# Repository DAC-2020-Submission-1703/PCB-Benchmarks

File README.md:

# PCB-Benchmarks

These are PCB benchmarks for automated layout as described in DAC 2020 submission 1703.
We have made efforts to anonymize this repo to facilitate the blind academic review process or DAC. The full repo will be updated with author information and so on after the review period.

## Metrics
The primary metrics for PCB layout are through-hole via count, required routing layers, required laser via layers, and area of the smallest rectangular bounding box. These metrics affect manufacturing cost.

A secondary metric is routed track length. It does not affect cost or correctness for these low-speed designs, but may be useful for evaluating the quality of a placement.

## Technical details
Each benchmark is manually placed and routed. 
To use as a layout benchmark, remove the manual routing and ignore the manual placement.

Each design is based on a real design that has been manufactured and tested. The designs in this repo have been modified from the originals to facillitate their use as layout benchmarks.

Each has a board outline in the Edge.Cuts layer. Each component has one or more courtyard polygons in the F.CrtYd and B.CrtYd layers if applicable.

Copper pours ("zones") have been removed from the designs. Nets that used zones for connectivity have been manually rerouted.

The manual routing jobs do not require laser vias; only through-hole vias are used.

Some components are "locked" as indicated by the locked keyword in their definition. These components must not be moved during automated placement.

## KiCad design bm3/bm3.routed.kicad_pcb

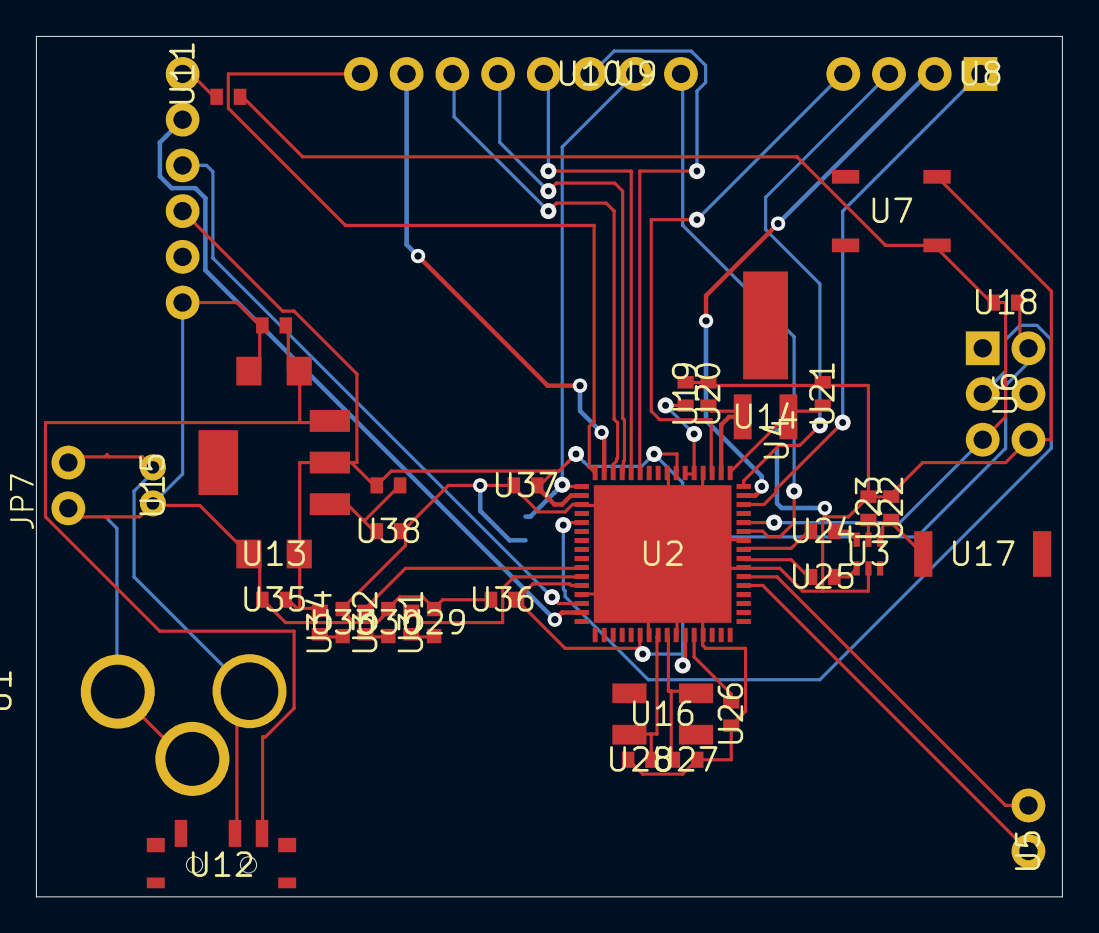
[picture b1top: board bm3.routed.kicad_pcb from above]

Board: 2 copper layers, 57.0 x 47.8 mm, 40 parts (0 on the bottom side), 38 nets.

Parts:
JP7: 1X02_NO_SILK
SJ1: SJ_2S-TRACE
U1: POWER_JACK_PTH_LOCK
U2: QFN-64
U3: BALUN
U4: SJ_2S-TRACE
U5, U9: 1X02_NO_SILK
U6: 2X3-NS
U7: TACTILE_SWITCH_SMD
U8: 1X04_NO_SILK
U10: 1X06_NS
U11: FTDI_BASIC
U12: SWITCH-SPST-SMD-A
U13: EIA3216
U14: CRYSTAL-32KHZ-SMD
U15: JST-2-PTH
U16: CRYSTAL-SMD-5X3
U17: ANTENNA-CHIP5
U18, U31, U32, U34, U38: 0402-RES
U19, U20, U21, U22, U23, U24, U25, U26, U27, U28, U35, U36, U37: 0402-CAP
U29, U30, U33: LED-0603

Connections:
3.3V: U2.23, U2.34, U2.44, U2.54, U2.59, U6.2, U11.VCC, U13.A, U18.2, U34.2, U35.1, U36.1, U37.1
A6: U2.5, U5.1
A7: U2.6, U5.2
AVDD: U2.60, U26.1
CLKI: SJ1.2, U2.33, U9.1
DVDD: U2.21, U2.22, U19.1
GND: JP7.1, SJ1.1, U1.GND, U1.GNDBREAK, U2.7, U2.10, U2.20, U2.24, U2.35, U2.45, U2.55, U2.58, U2.61, U2.65, U3.5, U4.1, U6.6, U7.3, U11.GND, U13.C, U15.1, U19.2, U20.2, U21.2, U22.1, U23.2, U26.2, U27.2, U28.2, U29.C, U30.C, U33.C, U35.2, U36.2, U37.2, U38.1
unnamed: U33.A, U34.1
unnamed: U2.57, U16.3, U27.1
unnamed: U2.56, U16.1, U28.1
unnamed: U2.18, U14.X1, U20.1
unnamed: U2.17, U14.X2, U21.1
unnamed: U3.2, U23.1
unnamed: U30.A, U32.1
unnamed: JP7.2, U1.PWR, U12.2, U15.2
unnamed: U3.4, U25.2
unnamed: U3.3, U24.1
unnamed: U29.A, U31.1
PB6: U2.42, U32.2
PB7: U2.43, U31.2
PD4: U2.29, U10.3
PD5: U2.30, U10.4
PD6: U2.31, U10.5
PD7: U2.32, U10.6
PG0: U2.14, U8.1
PG1: U2.15, U8.2
PG2: U2.16, U8.3
PG5: U2.19, U8.4
RESET: U2.12, U6.5, U7.1, U18.1
RFANT: U3.1, U17.FEED, U22.2
RFN: U2.9, U24.2
RFP: U2.8, U25.1
RX0: U2.46, U11.TXO
RX1: U2.27, U10.1
SCK: U2.37, U6.3
TST: U2.11, U4.2, U9.2
TX0: U2.47, U11.RXI
TX1: U2.28, U10.2

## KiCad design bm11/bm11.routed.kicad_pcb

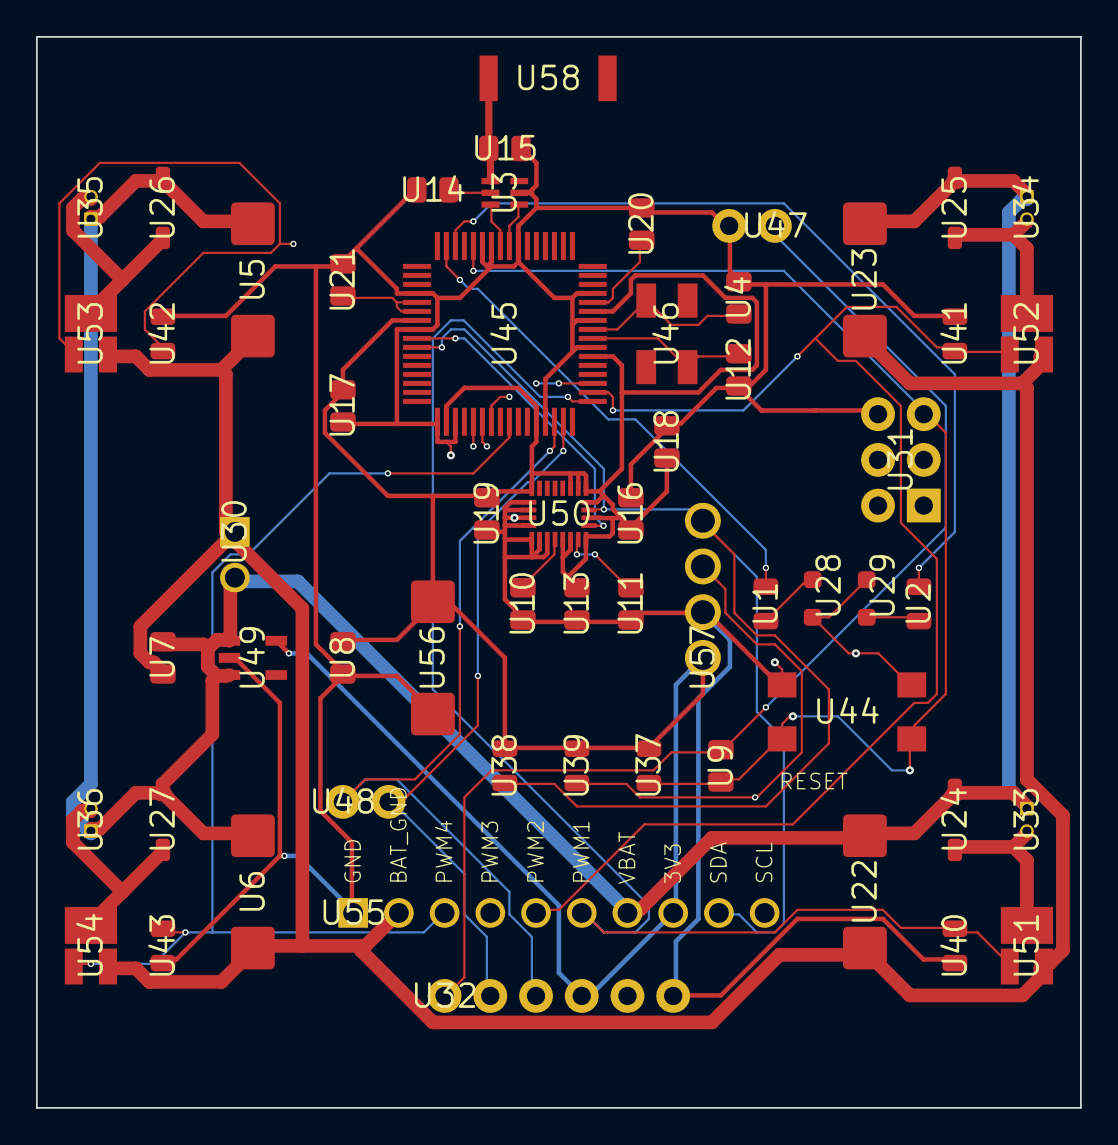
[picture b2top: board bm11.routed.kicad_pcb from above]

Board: 4 copper layers, 58.0 x 59.5 mm, 58 parts (0 on the bottom side), 35 nets.

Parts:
U1, U2, U37, U38, U39, U40, U41, U42, U43: RESC2012X60_HS
U3: BALUN
U4, U7, U8, U9, U10, U11, U12, U13, U14, U15, U16, U17, U18, U19, U20, U21: CAPC2012X140_HS
U5, U6, U22, U23, U56: CAPMP7343X310_HS
U24, U25, U26, U27: SOD3716X135_HS
U28, U29: LEDSC125X200X120-2_HS
U30: MALE_HEADER_2X1_0.1IN
U31: 2X3-NS
U32: FTDI_BASIC
U33, U34, U35, U36: MOLEX-0530470210
U44: 4.5MM_TACTILE_SWITCH_TL3305AF160QG
U45: QFN-64
U46: CRYSTAL-SMD-5X3
U47: FTDI_BASIC_2PIN_2
U48: FTDI_BASIC_2PIN_1
U49: SOT23-DBV
U50: NEW_IMU_MEDIUM
U51, U52, U53, U54: N_FET_SI2302CDS-T1-E3CT-ND
U55: HDRV10W63P254_10X1_2540X254H838_HS
U57: HDRVR4W80P254_1X4_1066X254X850B
U58: ANT-2.4GHZ-6.5X2.2MM

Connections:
3V3: U8.1, U13.1, U16.1, U17.1, U18.1, U19.1, U32.VCC, U37.2, U38.2, U39.2, U45.23, U45.34, U45.44, U45.54, U45.59, U49.5, U50.CS_A/G, U50.CS_M, U50.DEN_A/G, U50.SDO_A/G, U50.SDO_M, U50.VDD1, U50.VDD2, U50.VDDIO, U50.VDDIO2, U55.8, U56.1, U57.1
/DTR: U9.1, U32.DTR, U47.DTR
/LED1: U2.2, U45.14
/LED2: U1.2, U45.15
/MISO: U31.1, U45.39
/MOSI: U31.4, U45.38
/PWM1: U40.1, U45.49, U51.G, U55.6
/PWM2: U41.1, U45.50, U52.G, U55.5
/PWM3: U42.1, U45.51, U53.G, U55.4
/PWM4: U43.1, U45.41, U54.G, U55.3
/RESET: U9.2, U31.5, U37.1, U44.3, U44.4, U45.12
/RX0: U32.TXO, U45.46, U48.TXO
/SCK: U31.3, U45.37
/SCL: U39.1, U45.25, U50.SCL/SPC, U55.10, U57.3
/SDA: U38.1, U45.26, U50.SDA/SDI/SDO, U55.9, U57.4
/TX0: U32.RXI, U45.47, U48.RXI
BAT_GND: U5.2, U6.2, U7.2, U22.2, U23.2, U30.1, U51.S, U52.S, U53.S, U54.S, U55.2
GND: U3.5, U4.2, U8.2, U10.2, U11.2, U12.2, U13.2, U14.2, U15.2, U16.2, U17.2, U18.2, U19.2, U20.2, U21.2, U28.2, U29.1, U31.6, U32.GND, U40.2, U41.2, U42.2, U43.2, U44.1, U44.2, U45.7, U45.10, U45.11, U45.20, U45.24, U45.33, U45.35, U45.45, U45.55, U45.58, U45.61, U47.CTS, U49.2, U50.GND1, U50.GND2, U50.RES1, U50.RES2, U50.RES3, U50.RES4, U50.RES5, U55.1, U56.2, U57.2
unnamed: U3.1, U15.1, U58.FEED
unnamed: U3.2, U14.1
unnamed: U3.3, U45.9
unnamed: U3.4, U45.8
unnamed: U4.1, U45.57, U46.1
unnamed: U12.1, U45.56, U46.3
unnamed: U20.1, U45.60
unnamed: U21.1, U45.21, U45.22
unnamed: U10.1, U50.CAP
unnamed: U11.1, U50.C1
unnamed: U24.A, U33.2, U51.D
unnamed: U25.A, U34.2, U52.D
unnamed: U26.A, U35.2, U53.D
unnamed: U27.A, U36.2, U54.D
unnamed: U1.1, U28.1
unnamed: U2.1, U29.2
VBAT: U5.1, U6.1, U7.1, U22.1, U23.1, U24.C, U25.C, U26.C, U27.C, U30.2, U33.1, U34.1, U35.1, U36.1, U49.1, U49.3, U55.7

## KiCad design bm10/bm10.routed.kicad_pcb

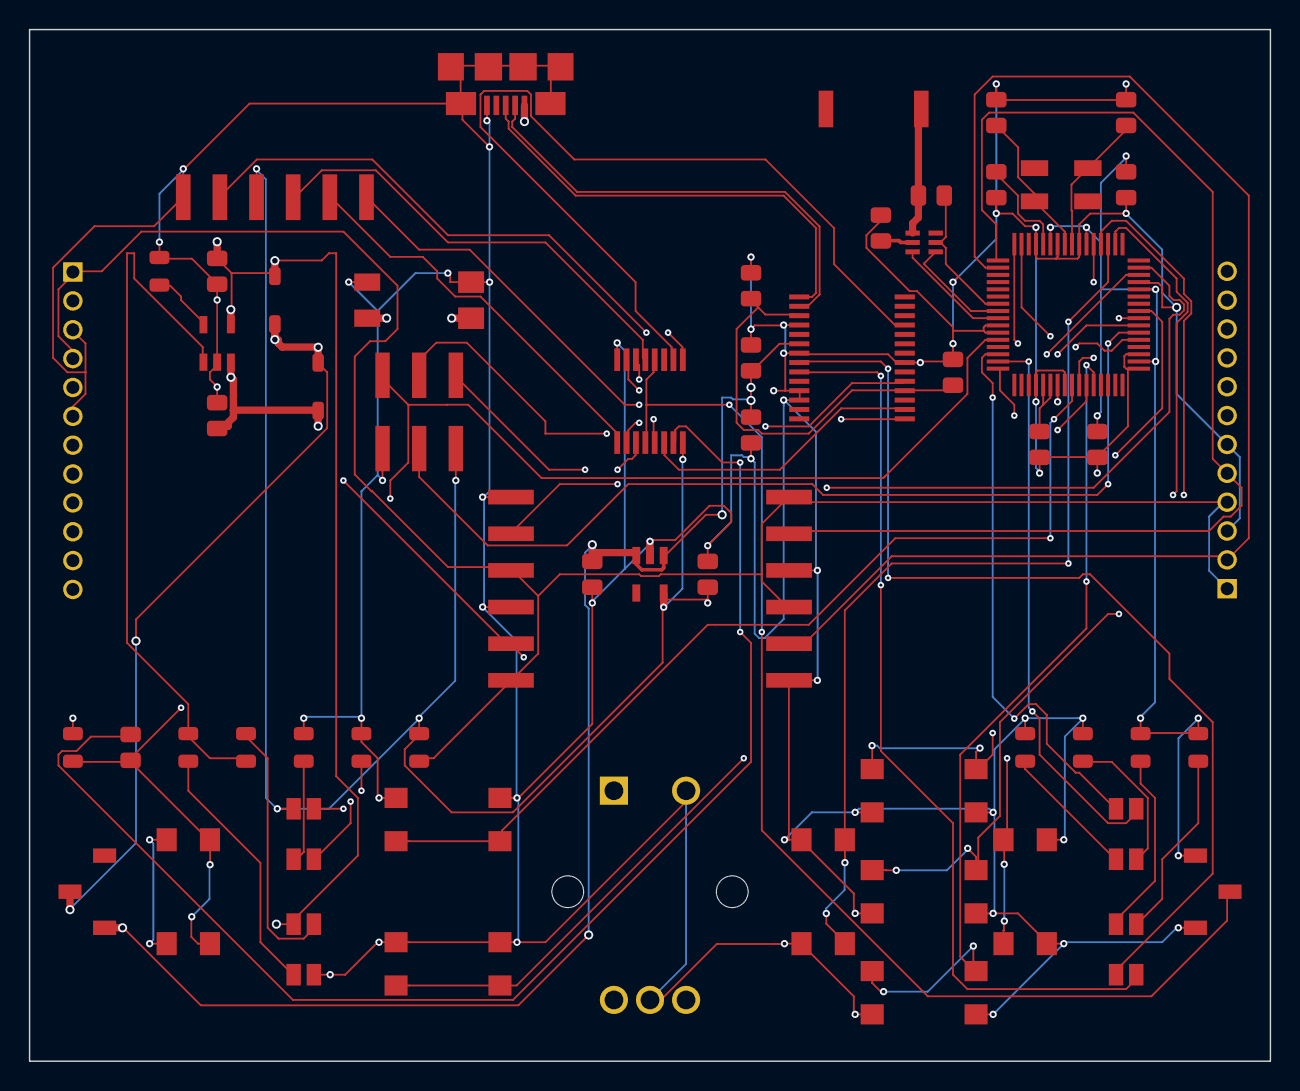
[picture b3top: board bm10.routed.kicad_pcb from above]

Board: 4 copper layers, 86.0 x 71.5 mm, 61 parts (0 on the bottom side), 63 nets.

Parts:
A1: ANTENNA-CHIP; ANT-2.4GHZ-6.5X2.2MM
B1, B4, B5, B6, B7, B8, B9, B10: PUSHBUTTON_-4.5X4.5; 4.5MM_TACTILE_SWITCH_TL3305AF160QG
B2: BALUN0805; BALUN
B3: BATTERY-SPRING-SMD; WIRE-TERMINAL-1X2-2.5MM-SMD-AVX-009276002021106
C1, C8, C9: 0.1uF; CAPC2012X140_HS
C2: 0.75pF; CAPC2012X140_HS
C3: 22pF; CAPC2012X140_HS
C4, C10, C11, C12, C13, C16, C17: 1uF; CAPC2012X140_HS
C5, C6, C7: 10uF; CAPC2012X140_HS
C14, C15: 12pF; CAPC2012X140_HS
D1, D4, D5, D6: LED-2X-GREEN_RED; LED-2X-LTST-C155
D2, D3: 360mV; SOD3716X135_HS
E1: ROTARY-ENCODER-W_BUTTON-BOURNS-PEC12R-4217F; BOURNS-PEC12R
J1: USB-MICROA-AMPHENOL-10118192-0001LF; USB-MICROA-10118192-0001LF
J2, J3: 2.4K; JST-13-PTH
J4: AVR_SPI_PRG_6-SMD; 2X3-SMD
J7, J8: FRSKY-GIMBAL-2X-SERVO-SMD; 2X-SERVO-SMD
JP1: FTDI_BASIC-SMD; FTDI-BASIC-SMD
R1, R3, R13, R14, R15, R16, R17, R18: 510; RESC2012X60_HS
R2: 10K; RESC2012X60_HS
R7: 2.2K; RESC2012X60_HS
R8: 1.2K; RESC2012X60_HS
S1, S2: POWER-SWITCH-MFS201N-9-Z-SMD-VERTICAL; JS102011JCQN
U1: 3.3V; SOT23-DBV
U2: MCP73831T-2ACI/OT; SOT23-5
U3: FT232RLSSOP; SSOP28DB
U4: ATMEGA128RFA1; QFN-64
U5: DPDT-X2; SOP65P640X110-16
Y1: CRYSTAL5X3; CRYSTAL-SMD-5X3

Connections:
3V3: C12.1, C16.1, C17.1, D4.A2, J4.2, JP1.VCC, R2.2, R8.2, R13.2, R14.2, S2.1, U1.5, U4.23, U4.34, U4.44, U4.54, U4.59, U5.16
/BTN1/SCL: B4.3, B4.4, U4.25
/BTN2/SDA: B5.3, B5.4, U4.26
/BTN_CENTER: B9.1, B9.2, U4.53
/BTN_DOWN: B10.1, B10.2, U4.28
/BTN_LEFT: B7.1, B7.2, U4.51
/BTN_RIGHT: B8.1, B8.2, U4.52
/BTN_UP: B6.1, B6.2, U4.50
/CTS: U3.11, U5.2
/CTS-1: JP1.CTS, U5.1
/DTR: U3.2, U5.14
/DTR-0: C1.2, U5.15
/DTR-1: JP1.DTR, U5.13
/E1-A: E1.A, U4.40
/E1-B: E1.B, U4.41
/E1-BUT: E1.BUTA, U4.27
/FTDI_OUT: C4.2, C9.1, U3.4, U3.17
/GREF: J2.1, J2.4, J3.1, J3.4, J7.1, J7.4, J8.1, J8.4, R8.1
/MISO: J4.1, U4.39
/MOSI: J4.4, U4.38
/PITCH: J3.V, J8.V, U4.2
/RESET: B1.1, B1.2, C1.1, J4.5, R2.1, U4.12
/RF: D4.A1, U4.16
/ROLL: J3.H, J8.H, U4.1
/RXI: U3.5, U5.10
/RXI-0: U4.47, U5.11
/RXI-1: JP1.RXI, U5.9
/RXLED: D5.C2, U3.22
/SCK: J4.3, U4.37
/THROTTLE: J2.V, J7.V, U4.64
/TXLED: D5.C1, U3.23
/TXO: U3.1, U5.6
/TXO-0: U4.46, U5.7
/TXO-1: JP1.TXO, U5.5
/USB_D_N: J1.2, U3.16
/USB_D_P: J1.3, U3.15
/VBUS: C5.1, D1.A2, D2.A, J1.1, U2.4
/VREG_IN: C7.1, C8.1, C10.1, S1.1, U1.1, U1.3, U3.20
/YAW: J2.H, J7.H, U4.63
GND: B1.3, B1.4, B2.5, B3.2A, B3.2B, B4.1, B4.2, B5.1, B5.2, B6.3, B6.4, B7.3, B7.4, B8.3, B8.4, B9.3, B9.4, B10.3, B10.4, C2.2, C3.1, C4.1, C5.2, C6.2, C7.2, C8.2, C9.2, C10.2, C11.2, C12.2, C13.2, C14.2, C15.2, C16.2, C17.2, D1.C1, E1.BUTB, E1.C, J1.5, J1.6, J1.7, J1.8, J1.9, J1.10, J1.11, J2.3, J2.6, J3.3, J3.6, J4.6, J7.3, J7.6, J8.3, J8.6, JP1.GND, R7.2, R15.1, R16.1, R17.1, R18.1, S2.3, U1.2, U2.2, U3.7, U3.18, U3.21, U3.25, U3.26, U4.7, U4.10, U4.11, U4.20, U4.24, U4.33, U4.35, U4.45, U4.55, U4.58, U4.61, U5.8
unnamed: A1.FEED, B2.1, C2.1
unnamed: B2.2, C3.2
unnamed: B2.3, U4.9
unnamed: B2.4, U4.8
unnamed: B3.1A, B3.1B, C6.1, D3.A, U2.3
unnamed: C11.1, U4.21, U4.22
unnamed: C13.1, U4.60
unnamed: C14.1, U4.57, Y1.3
unnamed: C15.1, U4.56, Y1.1
unnamed: D1.A1, R3.1
unnamed: D1.C2, R1.1
unnamed: D4.C1, R15.2
unnamed: D4.C2, R16.2
unnamed: D5.A1, R14.1
unnamed: D5.A2, R13.1
unnamed: D6.A1, U4.15
unnamed: D6.A2, U4.14
unnamed: D6.C1, R18.2
unnamed: D6.C2, R17.2
unnamed: R1.2, R3.2, U2.1
unnamed: R7.1, U2.5
unnamed: S2.2, U5.4, U5.12
VBAT: D2.C, D3.C, S1.2

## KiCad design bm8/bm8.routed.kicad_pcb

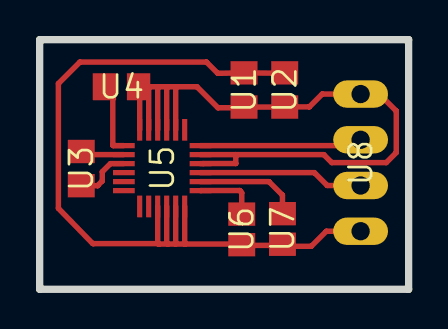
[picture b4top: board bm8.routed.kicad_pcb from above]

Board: 2 copper layers, 20.5 x 13.9 mm, 8 parts (0 on the bottom side), 9 nets.

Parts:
U1, U2, U3, U4: C0805
U5: LGA-24
U6, U7: R0805
U8: MA04-1

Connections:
/SCL: U5.21, U8.2
/SDA: U5.24, U8.3
GND: U1.2, U2.2, U4.1, U5.2, U5.3, U5.4, U5.5, U5.6, U5.22, U5.23, U8.4
unnamed: U3.1, U5.9
unnamed: U3.2, U5.8
unnamed: U4.2, U5.7
unnamed: U5.19, U6.1
unnamed: U5.20, U7.1
VDD: U1.1, U2.1, U5.15, U5.16, U5.17, U5.18, U6.2, U7.2, U8.1

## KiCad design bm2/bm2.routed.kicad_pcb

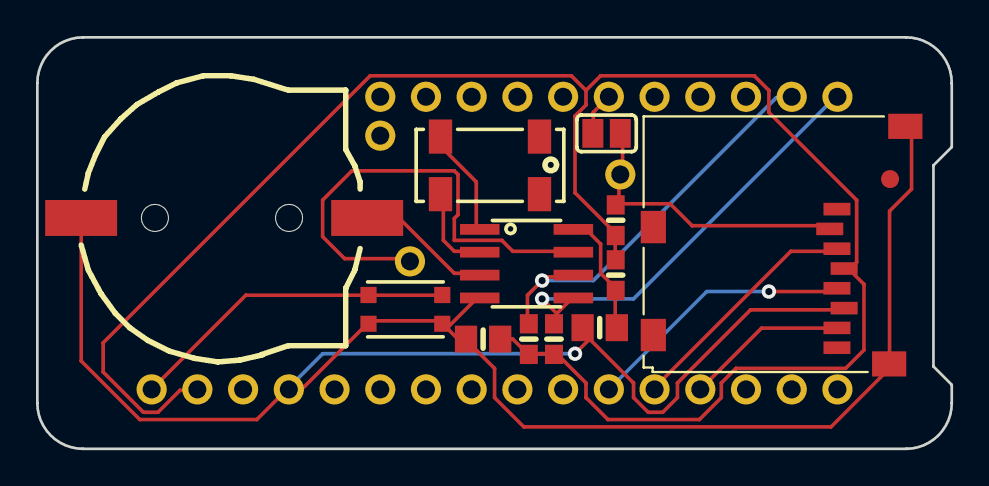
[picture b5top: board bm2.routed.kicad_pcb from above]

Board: 2 copper layers, 50.8 x 22.9 mm, 18 parts (0 on the bottom side), 15 nets.

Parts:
B1: cr1220; CR1220-2
C1, C2: 10uF; 0805-NO
FID1: FIDUCIAL_1MM
IC1: PCF8523T; SOIC8_150MIL
INT1: 1X01_ROUND
JP1: 1X11_ROUND
JP2: 1X16_ROUND
JP3: 1X01_ROUND
R1, R2: 10K; 0603-NO
R3: 100K; 0603-NO
R4: 1K; 0603-NO
SDCS: 1X01_ROUND
SJ1: SOLDERJUMPER_CLOSEDWIRE
SW1: KMR2; BTN_KMR2_4.6X2.8
X4: microsd; MICROSD
Y1: 32khz; CRYSTAL_8X3.8

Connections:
+3V3: C2.1, JP2.15, R1.2, R2.2, R3.2, R4.1, X4.4
CR1220: B1.+, IC1.3
CS: JP1.6, SJ1.1
GND: B1.-, C1.2, C2.2, IC1.4, JP2.13, SW1.A, SW1.A', X4.6, X4.MT1, X4.MT2
INT1: IC1.7, INT1.1
MISO: JP2.4, X4.7
MOSI: JP2.5, X4.3
unnamed: C1.1, IC1.8, R4.2
unnamed: IC1.1, Y1.P$4
unnamed: IC1.2, Y1.P$1
RESET: JP2.16, SW1.B, SW1.B'
SCK: JP2.6, X4.5
SCL: IC1.6, JP1.10, R2.1
SDA: IC1.5, JP1.11, R1.1
SD_CS: R3.1, SDCS.1, SJ1.2, X4.2

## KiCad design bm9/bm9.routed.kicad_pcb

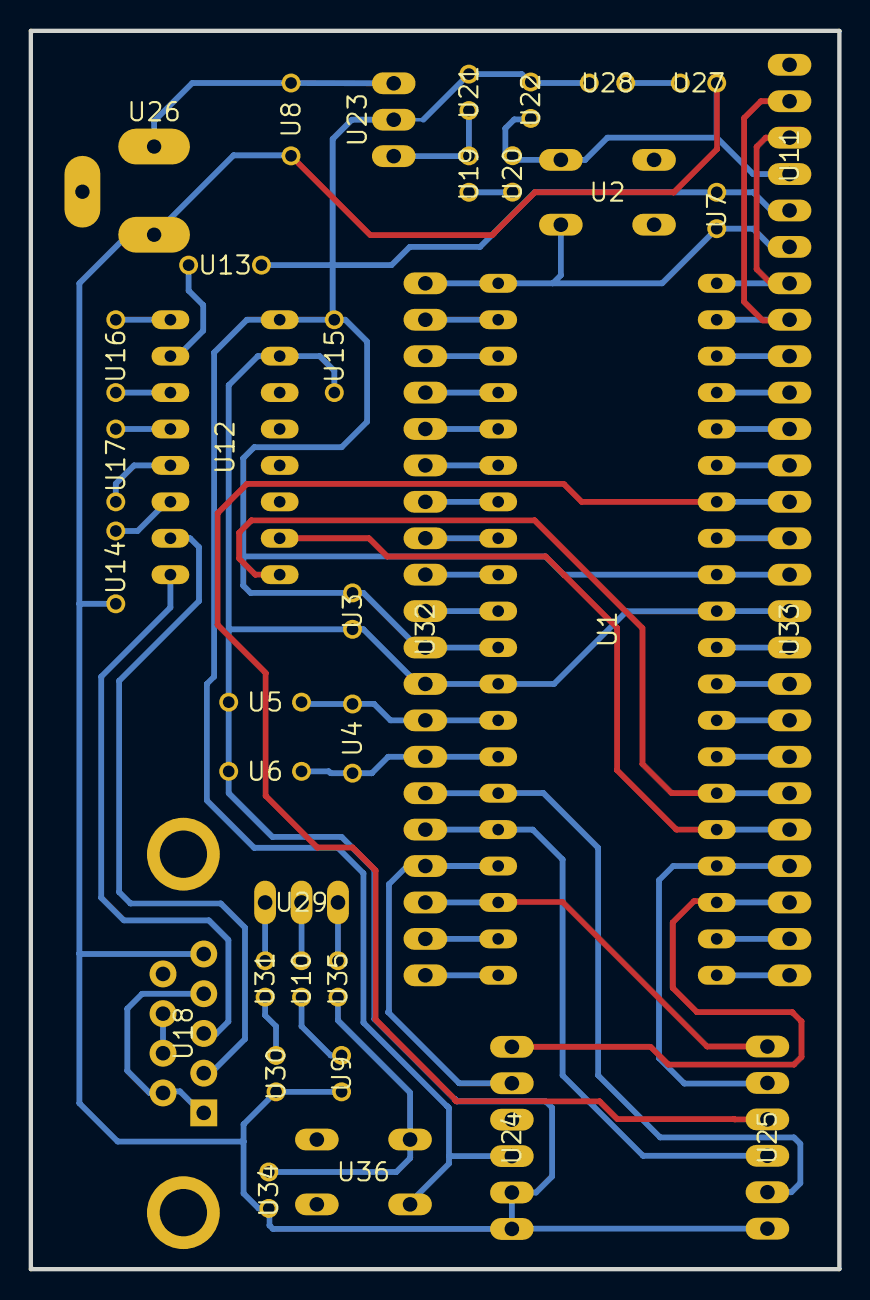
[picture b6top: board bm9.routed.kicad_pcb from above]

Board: 16 copper layers, 56.4 x 86.4 mm, 36 parts (0 on the bottom side), 58 nets.

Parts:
U1: DIL40
U2, U36: B3F-10XX
U3, U22: C025-024X044
U4: HC49_S
U5, U6, U13, U14, U15, U16, U17: C050-024X044
U7, U10, U19, U20, U21, U28, U31, U34, U35: V526-0
U8: C050-025X075
U9, U27, U30: LED3MM
U11, U24, U25: 1X06
U12: DIL16
U18: DB9
U23: 317TS
U26: 733980-62
U29: MA03-1
U32, U33: MA20-1

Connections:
/3.3V_SRC: U1.11, U1.32, U3.1, U7.1, U11.2, U12.16, U13.2, U15.1, U21.2, U22.1, U23.2, U24.3, U28.1, U32.10, U33.9, U36.1
/MRF_CS: U1.17, U24.5, U32.4
/MRF_INT: U1.34, U25.3, U33.7
/MRF_RESET: U1.15, U25.5, U32.6
/MRF_SCK: U1.18, U25.1, U32.3
/MRF_SDI: U1.23, U24.6, U33.18
/MRF_SDO: U1.24, U25.2, U33.17
/MRF_WAKE: U1.16, U25.4, U32.5
/N$17: U1.26, U12.9, U33.15
/N$21: U1.25, U12.10, U33.16
/OS1: U1.13, U4.1, U5.1, U32.8
/OSC2: U1.14, U4.2, U6.1, U32.7
GND: U1.12, U1.31, U2.1, U3.2, U5.2, U6.2, U8.2, U9.K, U11.3, U12.15, U14.1, U15.2, U18.5, U20.1, U22.2, U24.1, U24.2, U25.6, U26.1, U27.K, U30.K, U32.9, U33.10, U34.2
unnamed: U12.2, U13.1
unnamed: U12.6, U14.2
unnamed: U12.1, U16.1
unnamed: U12.3, U16.2
unnamed: U12.4, U17.1
unnamed: U12.5, U17.2
unnamed: U8.1, U23.3, U26.2
unnamed: U12.7, U18.2
unnamed: U12.8, U18.3
unnamed: U1.1, U2.3, U7.2, U11.1, U32.20
unnamed: U1.2, U32.19
unnamed: U1.3, U32.18
unnamed: U1.4, U32.17
unnamed: U1.5, U32.16
unnamed: U1.6, U32.15
unnamed: U1.7, U32.14
unnamed: U1.8, U32.13
unnamed: U1.9, U32.12
unnamed: U1.10, U32.11
unnamed: U1.19, U32.2
unnamed: U1.20, U32.1
unnamed: U1.21, U33.20
unnamed: U1.22, U33.19
unnamed: U1.27, U33.14
unnamed: U1.28, U33.13
unnamed: U1.29, U33.12
unnamed: U1.30, U33.11
unnamed: U1.33, U33.8
unnamed: U1.35, U33.6
unnamed: U1.36, U33.5
unnamed: U1.37, U33.4
unnamed: U1.38, U33.3
unnamed: U1.39, U11.5, U33.2
unnamed: U1.40, U11.4, U33.1
unnamed: U19.2, U21.1, U23.1
unnamed: U27.A, U28.2
unnamed: U30.A, U31.2
unnamed: U9.A, U10.2
unnamed: U34.1, U35.2, U36.3
unnamed: U29.3, U35.1
unnamed: U10.1, U29.2
unnamed: U29.1, U31.1
unnamed: U19.1, U20.2
unnamed: U18.1, U18.4, U18.6
unnamed: U18.7, U18.8

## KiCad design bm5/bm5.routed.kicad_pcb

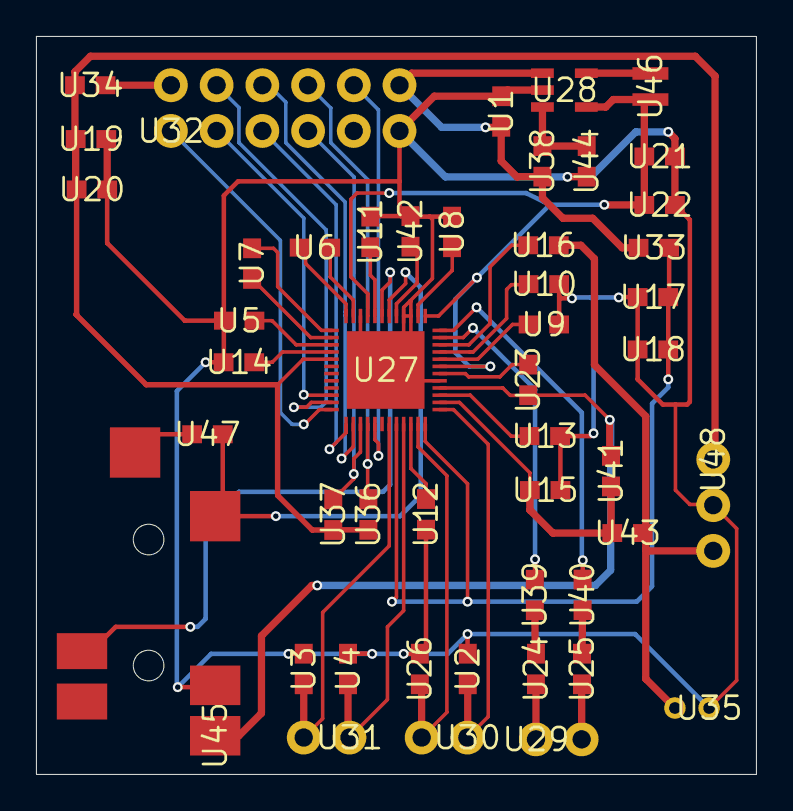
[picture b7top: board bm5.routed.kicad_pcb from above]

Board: 2 copper layers, 40.0 x 41.0 mm, 48 parts (0 on the bottom side), 47 nets.

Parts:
U1, U2, U3, U4, U5, U6, U7, U8, U9, U10, U11, U12, U13, U14, U15, U16, U17, U18, U19, U20, U21, U22, U23, U24, U25, U26, U33, U34, U36, U37, U38, U39, U40, U41, U42, U43, U44, U47: 0603
U27: QFN50P700X700X100-49N
U28: SOT95P284X122-5N
U29, U30, U31: 1X02
U32: 2X6
U35: CMC-2242PBL-A
U45: SJ-43514-SMT-TR
U46: NRH2412T2R2MNGH
U48: 1X03

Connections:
3.3V: U32.2, U34.2
5V: U1.2, U28.1, U32.12, U33.2, U38.1
/1.8VDD: U21.1, U22.1, U27.7, U27.13, U27.21, U28.4, U46.2
/3.3VDD: U19.1, U20.1, U27.29, U34.1, U36.1, U37.1, U48.1
/CPVREF: U27.17, U42.1
/HPOL: U27.18, U45.2, U47.1
/HPOR: U27.19, U45.3
/IN1P: U23.1, U27.4, U41.2, U45.1
/IN2P: U16.1, U35.2, U43.2, U48.3
/LOUTL: U27.11, U39.1
/LOUTR: U27.12, U40.1
/MICBIAS1: U15.2, U27.2, U41.1, U43.1
/SPKVDD: U17.1, U18.1, U27.44, U27.48, U33.1
/SPOLN: U26.1, U27.47, U30.2
/SPOLP: U2.1, U27.1, U30.1
/SPORN: U3.1, U27.43, U31.2
/SPORP: U4.1, U27.45, U31.1
/XADUIO_I2S0_BCLK: U27.37, U32.5
/XADUIO_I2S0_LRCKL: U27.36, U32.1
/XADUIO_SCL: U27.39, U32.7, U37.2
/XAUDIO_I2S0_DIN: U27.35, U32.4
/XAUDIO_I2S0_DOUT: U27.34, U32.3
/XAUDIO_I2S0_MCLK: U27.38, U32.6
/XAUDIO_IRQ: U27.41, U32.10
/XAUDIO_SDA: U27.40, U32.8, U36.2
GND: U1.1, U2.2, U3.2, U4.2, U5.2, U8.1, U9.1, U10.1, U11.2, U12.1, U13.1, U14.1, U15.1, U17.2, U18.2, U19.2, U20.2, U21.2, U22.2, U26.2, U27.5, U27.15, U27.16, U27.22, U27.49, U28.2, U32.11, U35.1, U42.2, U44.1, U45.4, U48.2
unnamed: U11.1, U27.20
unnamed: U23.2, U27.6
unnamed: U24.1, U39.2
unnamed: U24.2, U29.1
unnamed: U25.1, U40.2
unnamed: U25.2, U29.2
unnamed: U5.1, U27.27
unnamed: U6.1, U27.24
unnamed: U6.2, U27.23
unnamed: U7.1, U27.25
unnamed: U7.2, U27.26
unnamed: U8.2, U27.14
unnamed: U9.2, U27.8
unnamed: U10.2, U27.9
unnamed: U12.2, U27.46
unnamed: U13.2, U27.3
unnamed: U14.2, U27.28
unnamed: U16.2, U27.10
unnamed: U28.3, U38.2, U44.2
unnamed: U28.5, U46.1
unnamed: U45.5, U47.2

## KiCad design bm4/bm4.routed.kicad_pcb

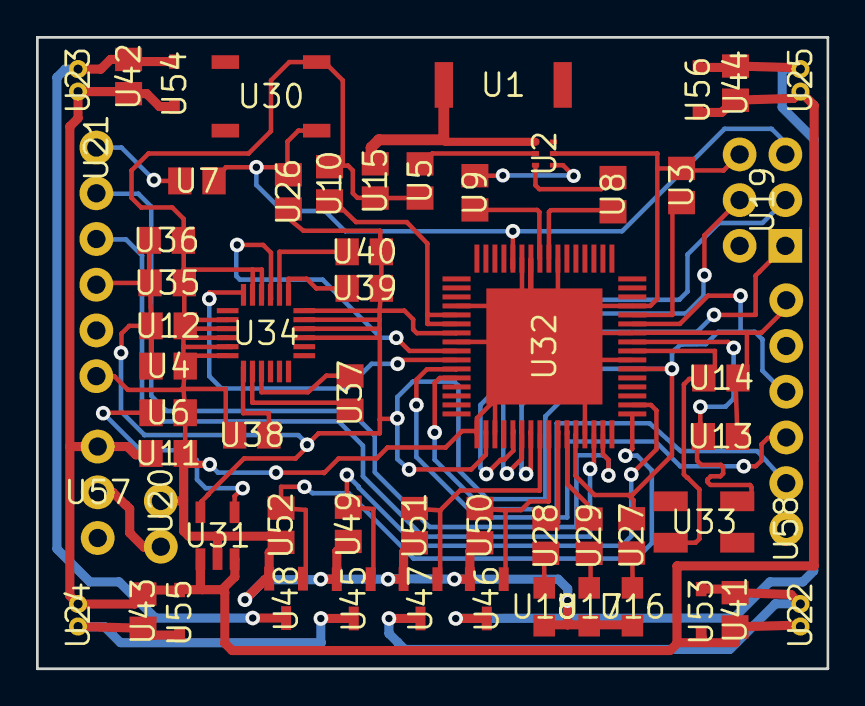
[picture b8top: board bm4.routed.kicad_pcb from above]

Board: 16 copper layers, 43.9 x 35.1 mm, 58 parts (0 on the bottom side), 44 nets.

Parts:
U1: ANTENNA-CHIP5
U2: BALUN-0805
U3, U4, U5, U6, U7, U8, U9, U10, U11, U12, U13, U14, U15, U35, U36, U37, U38, U41, U42, U43, U44: C0805
U16, U17, U18: CHIP-LED0805
U19: 2X3-NS
U20: 1X02
U21, U58: FTDI_BASIC
U22, U23, U24, U25: 653002114822
U26, U27, U28, U29, U39, U40, U49, U50, U51, U52: R0805
U30: TACTILE_SWITCH_SMD
U31: SOT23-DBV
U32: QFN-64
U33: CRYSTAL-SMD-5X3
U34: LGA-24
U45, U46, U47, U48: CONTROLLER_SOT95P237X112-3N
U53, U54, U55, U56: SOD323_ST
U57: SWITCH-SPDT

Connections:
3.3V: U4.1, U12.1, U21.VCC, U26.2, U27.2, U31.5, U32.23, U32.34, U32.44, U32.54, U32.59, U34.15, U34.16, U34.17, U34.18, U35.1, U36.1, U39.2, U40.2, U58.VCC
/MISO: U19.1, U32.39
/MOSI: U19.4, U32.38
/PB4: U32.40, U47.1, U51.1
/PB5: U32.41, U46.1, U50.1
/PB6: U28.2, U32.42
/PB7: U29.2, U32.43
/PE3: U32.49, U48.1, U52.1
/PE4: U32.50, U45.1, U49.1
/RESET: U7.2, U19.5, U26.1, U30.1, U32.12
/RFANT: U1.FEED, U2.1, U15.2
/RX0: U21.TXO, U32.46
/RX1: U32.27, U58.TXO
/SCK: U19.3, U32.37
/SCL: U32.25, U34.21
/SDA: U32.26, U34.24
/TX0: U21.RXI, U32.47
/TX1: U32.28, U58.RXI
/VBAT: U11.1, U22.1, U23.1, U24.1, U25.1, U31.1, U31.3, U41.1, U42.1, U43.1, U44.1, U53.C, U54.C, U55.C, U56.C, U57.3
GND: U2.5, U3.2, U4.2, U5.2, U6.2, U10.2, U11.2, U12.2, U13.2, U14.2, U15.1, U16.C, U17.C, U18.C, U19.6, U20.1, U21.GND, U30.3, U31.2, U32.7, U32.10, U32.11, U32.20, U32.24, U32.33, U32.35, U32.45, U32.55, U32.58, U32.61, U32.65, U34.2, U34.3, U34.4, U34.5, U34.6, U34.22, U34.23, U35.2, U36.2, U38.1, U45.2, U46.2, U47.2, U48.2, U49.2, U50.2, U51.2, U52.2, U58.GND
unnamed: U18.A, U28.1
unnamed: U2.2, U5.1
unnamed: U2.3, U8.2
unnamed: U2.4, U9.1
unnamed: U17.A, U29.1
unnamed: U3.1, U32.60
unnamed: U10.1, U32.21, U32.22
unnamed: U13.1, U32.57, U33.3
unnamed: U14.1, U32.56, U33.1
unnamed: U22.2, U41.2, U47.3, U53.A
unnamed: U23.2, U42.2, U48.3, U54.A
unnamed: U6.1, U31.4
unnamed: U24.2, U43.2, U45.3, U55.A
unnamed: U25.2, U44.2, U46.3, U56.A
unnamed: U7.1, U21.DTR
unnamed: U8.1, U32.8
unnamed: U9.2, U32.9
unnamed: U34.9, U37.1
unnamed: U34.8, U37.2
unnamed: U34.7, U38.2
unnamed: U20.2, U57.2
unnamed: U16.A, U27.1
unnamed: U34.19, U39.1
unnamed: U34.20, U40.1
